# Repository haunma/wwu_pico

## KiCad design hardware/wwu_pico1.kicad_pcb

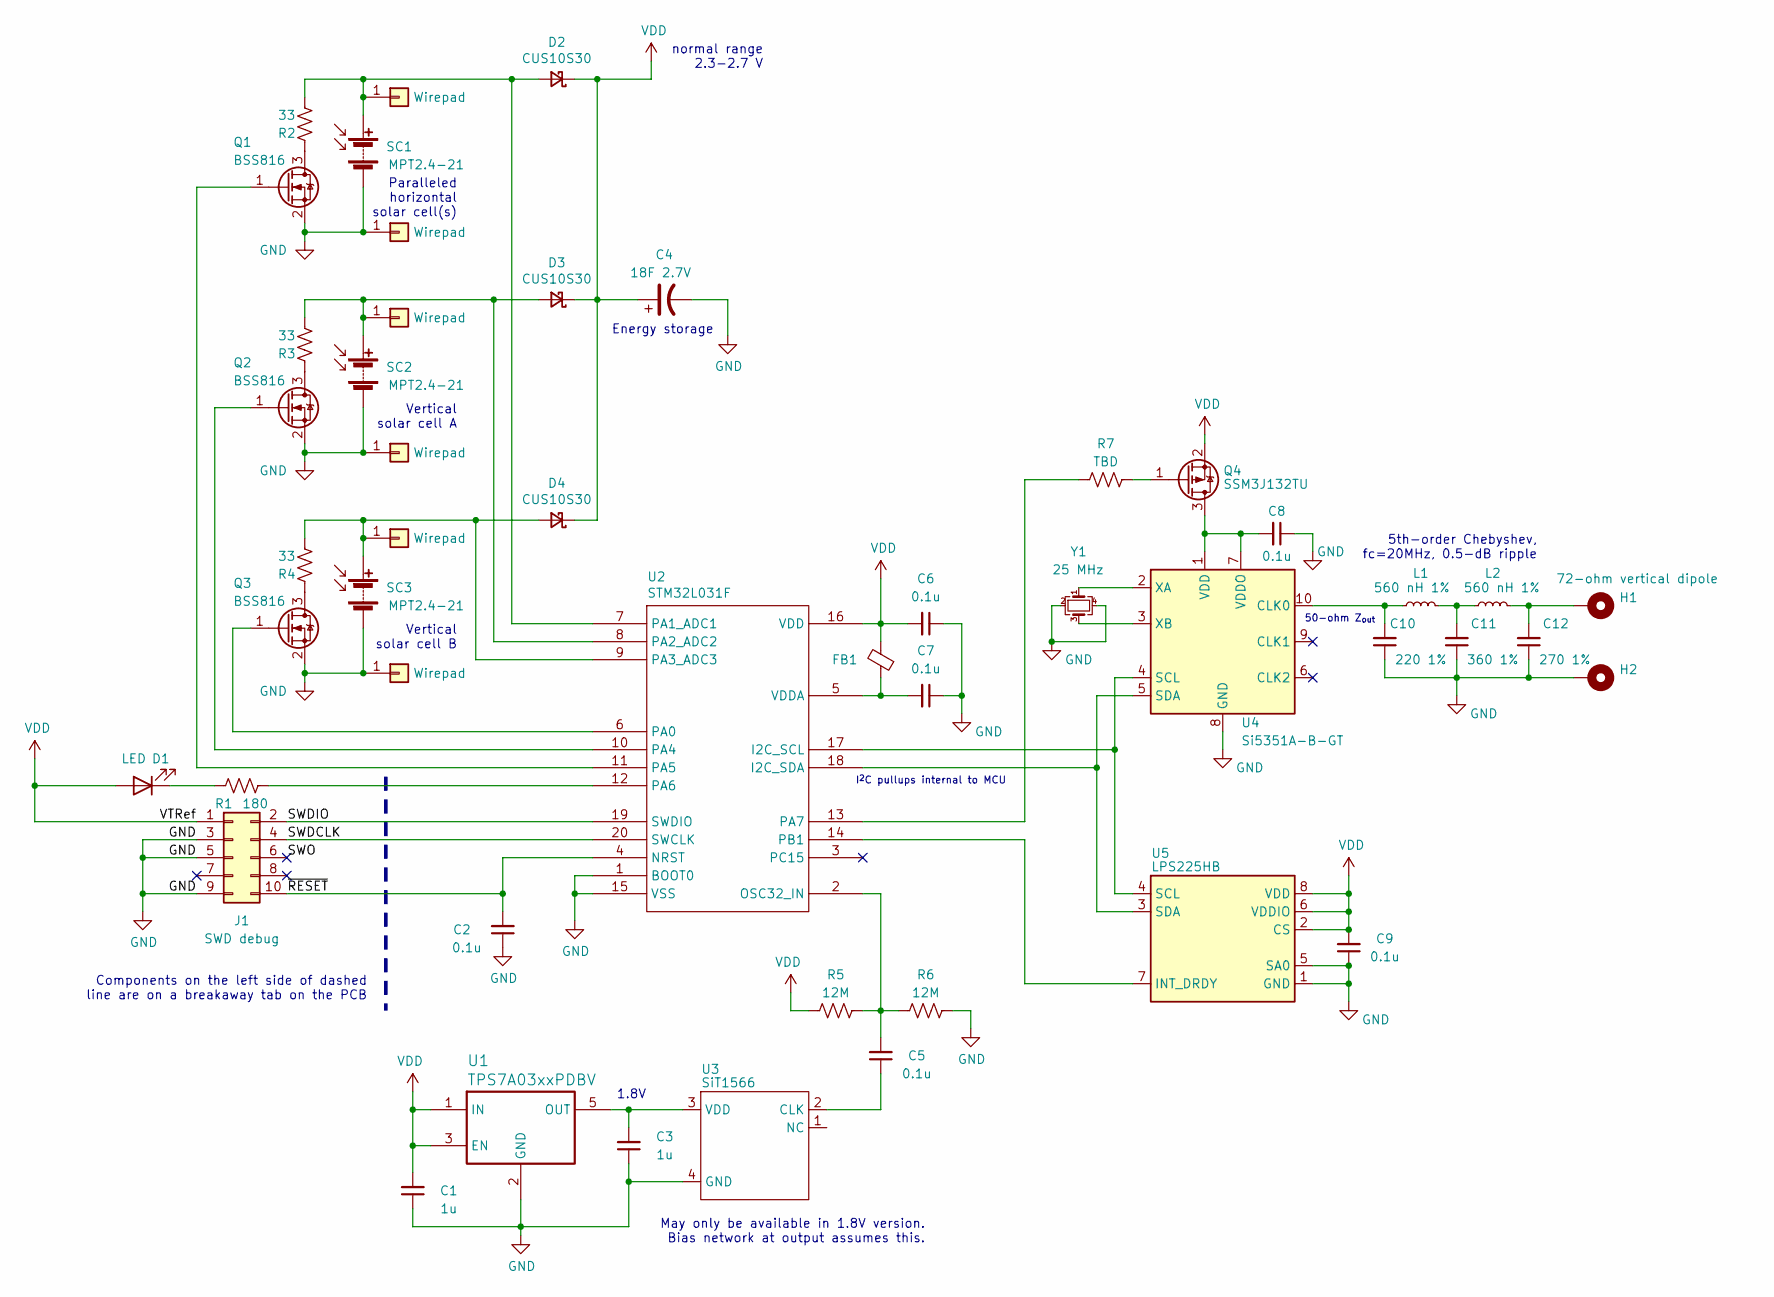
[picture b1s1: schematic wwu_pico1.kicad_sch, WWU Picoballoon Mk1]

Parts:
C1, C3: 1u; C_0603
C2, C5, C6, C7, C8, C9: 0.1u; C_0603
C4: 18F 2.7V; CP_Radial_D12.5mm_P5.00mm
C10: 220 1%; C_0603
C11: 360 1%; C_0603
C12: 270 1%; C_0603
D1: LED; LED_0603
D2, D3, D4: CUS10S30; D_SOD-323_HandSoldering
FB1: Ferrite_Bead_Small; R_0603
H1, H2: 72-ohm vertical dipole; SolderWirePad_single_0-8mmDrill
J1: SWD debug; Pin_Header_Straight_2x05_Pitch1.27mm
J2, J3, J4, J5, J6, J7: Wirepad; SolderWirePad_single_0-8mmDrill
L1, L2: 560 nH 1%; L_Abracon_ASPI-3012S
Q1, Q2, Q3: BSS816; SOT-323_SC-70
Q4: SSM3J132TU; SOT-323_SC-70
R1: 180; R_0603
R2, R3, R4: 33; R_0603
R5, R6: 12M; R_0603
R7: TBD; R_0603
SC1, SC2, SC3: MPT2.4-21
U1: TPS7A03xxPDBV; SOT-23-5
U2: STM32L031F; TSSOP-20_4.4x6.5mm_Pitch0.65mm
U3: SiT1566; SiTime_SiT1566
U4: Si5351A-B-GT; MSOP-10_3x3mm_Pitch0.5mm
U5: LPS225HB; ST_HLGA_8L
Y1: 25 MHz; Crystal_SMD_2016-4pin_2.0x1.6mm

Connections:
/SWDCLK: J1.4, U2.20 (SWCLK)
/SWDIO: J1.2, U2.19 (SWDIO)
/SWO: J1.6
/~RESET: C2.2, J1.10, U2.4 (NRST)
GND: C1.1, C2.1, C3.1, C4.2, C6.1, C7.1, C8.1, C9.1, C10.1, C11.1, C12.1, H2.1, J1.3, J1.5, J1.9, J3.1, J5.1, J7.1, Q1.2 (S), Q2.2 (S), Q3.2 (S), R6.1, SC1.2 (-), SC2.2 (-), SC3.2 (-), U1.2 (GND), U2.1 (BOOT0), U2.15 (VSS), U3.4 (GND), U4.8 (GND), U5.1 (GND), U5.5 (SA0), Y1.2, Y1.4
unnamed: C3.2, U1.5 (OUT), U3.3 (VDD)
unnamed: C5.1, U3.2 (CLK)
unnamed: C5.2, R5.1, R6.2, U2.2 (OSC32_IN)
unnamed: C7.2, FB1.1, U2.5 (VDDA)
unnamed: C8.2, Q4.3 (D), U4.1 (VDD), U4.7 (VDDO)
unnamed: C10.2, L1.1, U4.10 (CLK0)
unnamed: C11.2, L1.2, L2.1
unnamed: C12.2, H1.1, L2.2
unnamed: D1.1 (K), R1.1
unnamed: D2.2 (A), J2.1, R2.2, SC1.1 (+), U2.7 (PA1_ADC1)
unnamed: D3.2 (A), J4.1, R3.2, SC2.1 (+), U2.8 (PA2_ADC2)
unnamed: D4.2 (A), J6.1, R4.2, SC3.1 (+), U2.9 (PA3_ADC3)
unnamed: Q1.1 (G), U2.11 (PA5)
unnamed: Q1.3 (D), R2.1
unnamed: Q2.1 (G), U2.10 (PA4)
unnamed: Q2.3 (D), R3.1
unnamed: Q3.1 (G), U2.6 (PA0)
unnamed: Q3.3 (D), R4.1
unnamed: Q4.1 (G), R7.1
unnamed: R1.2, U2.12 (PA6)
unnamed: R7.2, U2.13 (PA7)
unnamed: U2.14 (PB1), U5.7 (INT_DRDY)
unnamed: U2.17 (I2C_SCL), U4.4 (SCL), U5.4 (SCL)
unnamed: U2.18 (I2C_SDA), U4.5 (SDA), U5.3 (SDA)
unnamed: U4.2 (XA), Y1.1
unnamed: U4.3 (XB), Y1.3
VDD: C1.2, C4.1, C6.2, C9.2, D1.2 (A), D2.1 (K), D3.1 (K), D4.1 (K), FB1.2, J1.1, Q4.2 (S), R5.2, U1.1 (IN), U1.3 (EN), U2.16 (VDD), U5.2 (CS), U5.6 (VDDIO), U5.8 (VDD)

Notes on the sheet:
Components on the left side of dashed line are on a breakaway tab on the PCB
Paralleled horizontal solar cell(s)
Vertical solar cell A
Vertical solar cell B
1.8V
Energy storage
normal range 2.3-2.7 V
May only be available in 1.8V version. Bias network at output assumes this.
I^{2}C pullups internal to MCU
50-ohm Z_{out}
5th-order Chebyshev, fc=20MHz, 0.5-dB ripple

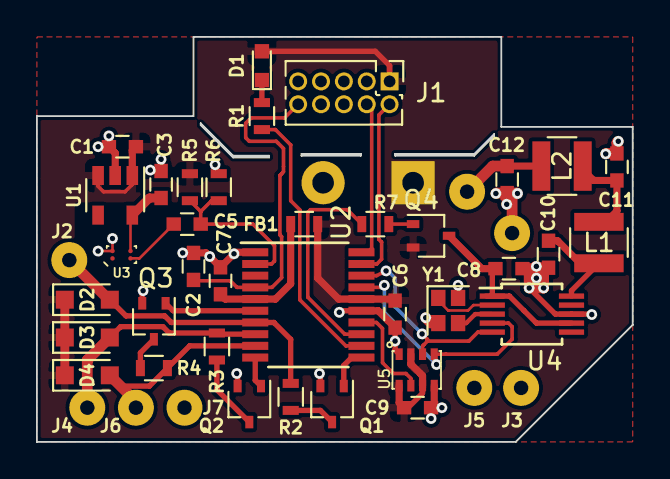
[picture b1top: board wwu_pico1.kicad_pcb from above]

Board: 2 copper layers, 33.1 x 22.5 mm, 45 parts (1 on the bottom side), 31 nets.
